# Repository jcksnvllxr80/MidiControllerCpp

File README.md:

# MidiController (C++)

Portable C++17 rewrite of a guitar-pedal MIDI controller's brain, ported from the
Raspberry Pi Python version. Hexagonal design: a hardware-free domain core with all
I/O behind interfaces, so the same code runs on the desktop sim now and a
microcontroller later.

Status: domain core + config + simulator are done and tested; the microcontroller
firmware (Pico 2 W / RP2350) builds and is under hardware bring-up. (The editor app
is a separate project.)
Roadmap: [docs/plan.md](docs/plan.md).

## Build, test, run (WSL)

The **firmware** builds with CMake + the Pico SDK; the **simulator** and the **tests**
build with `g++` (C++17) — GoogleTest and nlohmann/json are vendored, so the host
build has no other dependencies.

```sh
make build       # firmware  -> build-pico/midicontroller_pico.uf2  (Pico 2 W; needs PICO_SDK_PATH)
make build-sim   # simulator  -> build/midicontroller
make test        # build & run all tests (unit + mock + e2e)
make run         # run the simulator on data/ (scripted demo)
make clean       # remove desktop build/ ;  make pico-clean removes build-pico/
```

Flashing and wiring: [docs/mcu.md](docs/mcu.md) and [docs/wiring.md](docs/wiring.md).

## CI & releases

GitHub Actions ([`.github/workflows/ci.yml`](.github/workflows/ci.yml)) runs the host test
suite and builds the firmware `.uf2` on every push and PR. On a push to `master`, once both
pass, it cuts a GitHub **Release** `v<VERSION>` (from the [`VERSION`](VERSION) file) with the
versioned `.uf2` attached — **only when `VERSION` changed** (the tag is new). To ship: bump
`VERSION` and merge to `master`.

## Layout

```
include/mc/   headers: domain/ ports/ config/ adapters/ app/
src/          implementations + main.cpp
data/         config as JSON: midi_controller.json, pedals/, songs/, sets/
tests/        unit/ mock/ e2e/ support/
tools/        yaml2json.py (YAML→JSON), embed_data.py (bake data into flash), gen_font.py, gen_wiring_excalidraw.py
third_party/  vendored googletest + nlohmann/json
docs/         plan, architecture, domain, midi-protocol, config-format, mcu, wiring, wifi-app-handoff
```

## Notes

- The MIDI output matches the original Python byte-for-byte, including its quirks
  (e.g. `Set Preset`'s `cc:0` bank is never sent). See [docs/midi-protocol.md](docs/midi-protocol.md).
- `data/*.json` is generated from the original YAML by `tools/yaml2json.py` and committed.

## Docs

- [docs/architecture.md](docs/architecture.md) — ports & adapters + data-flow diagrams (mermaid)
- [docs/domain.md](docs/domain.md) — the core modules
- [docs/midi-protocol.md](docs/midi-protocol.md) — byte construction & dispatch
- [docs/config-format.md](docs/config-format.md) — JSON config reference
- [docs/mcu.md](docs/mcu.md) — firmware build/flash, adapters, hardware status
- [docs/wiring.md](docs/wiring.md) — Pico 2 W pin map, parts, power (+ `wiring.excalidraw` diagram)
- [docs/wifi-app-handoff.md](docs/wifi-app-handoff.md) — editor-app protocol contract (WiFi, device discovery, firmware update)

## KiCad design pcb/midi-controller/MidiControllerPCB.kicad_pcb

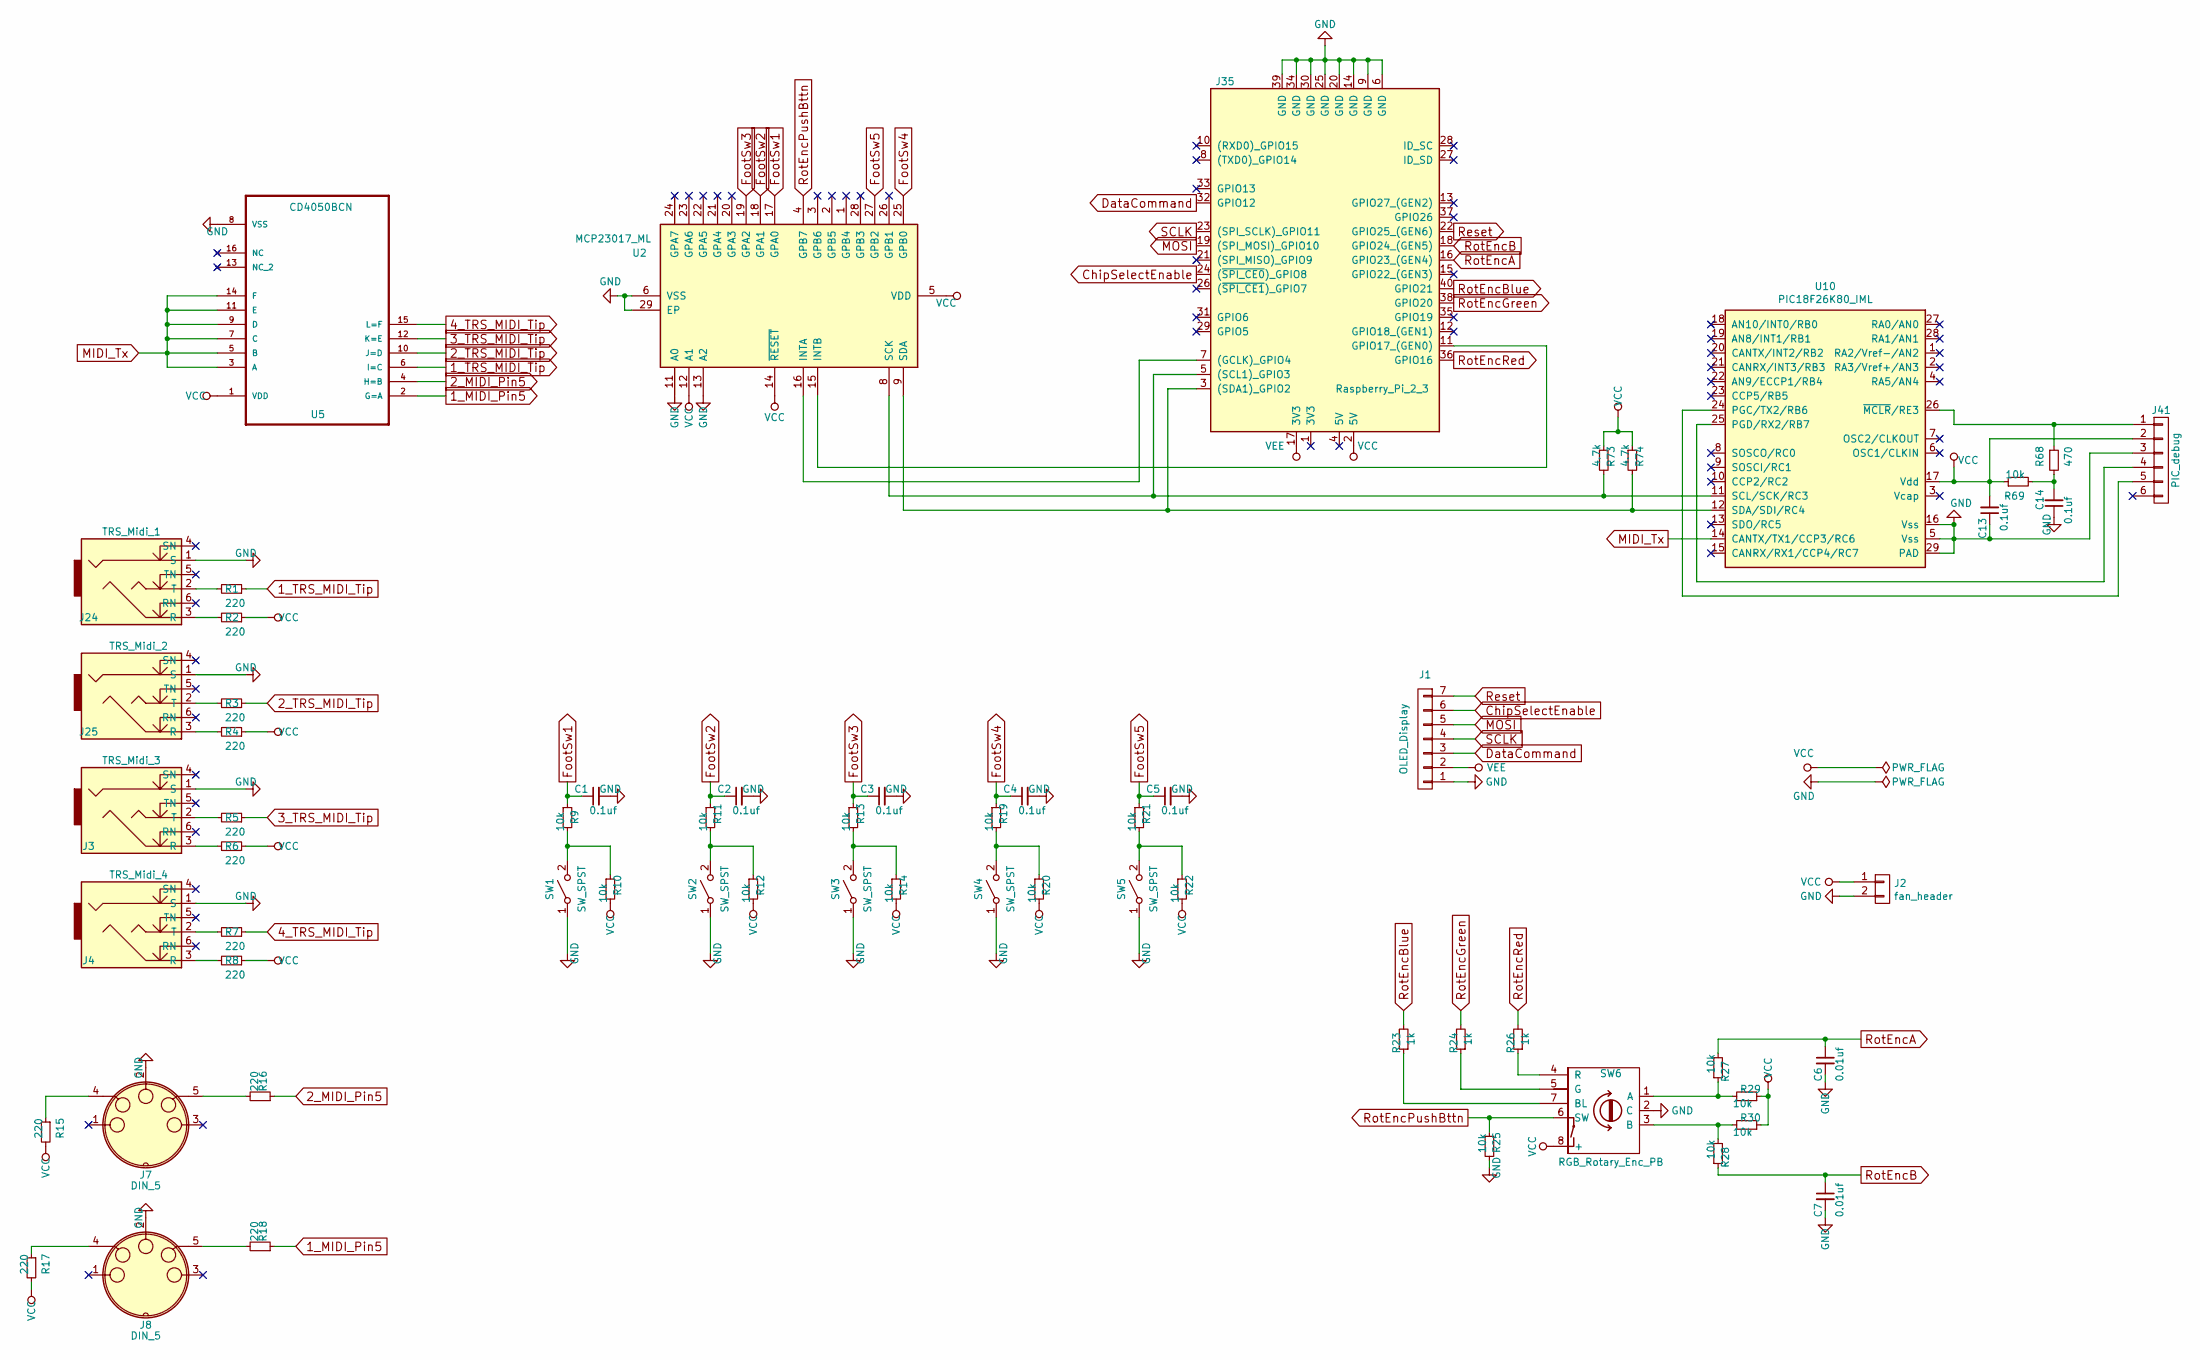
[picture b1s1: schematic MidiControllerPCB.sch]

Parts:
C1, C2, C3, C4, C5, C13, C14: 0.1uf; C_1206_HandSoldering
C6, C7: 0.01uf; C_1206_HandSoldering
J1: OLED_Display; Pin_Header_Straight_1x07_Pitch1.27mm
J2: fan_header; Pin_Header_Straight_1x02_Pitch2.54mm
J3: TRS_Midi_3; NRJ6HM-1-PRE
J4: TRS_Midi_4; NRJ6HM-1-PRE
J7, J8: DIN_5; Midi-Connector
J24: TRS_Midi_1; NRJ6HM-1-PRE
J25: TRS_Midi_2; NRJ6HM-1-PRE
J35: Raspberry_Pi_2_3; Pin_Header_Straight_2x20_Pitch2.54mm
J41: PIC_debug; Pin_Header_Straight_1x06_Pitch2.54mm
R1, R2, R3, R4, R5, R6, R7, R8, R15, R16, R17, R18: 220; R_1206_HandSoldering
R9, R10, R11, R12, R13, R14, R19, R20, R21, R22, R25, R27, R28, R29, R30, R69: 10k; R_1206_HandSoldering
R23, R24, R26: 1k; R_1206_HandSoldering
R68: 470; R_1206_HandSoldering
R73, R74: 4.7k; R_1206_HandSoldering
SW1, SW2, SW3, SW4, SW5: SW_SPST; Pin_Header_Straight_1x02_Pitch2.54mm
SW6: RGB_Rotary_Enc_PB; Pin_Header_Straight_2x04_Pitch2.54mm
U2: MCP23017_ML; QFN-28-1EP_6x6mm_Pitch0.65mm
U5: CD4050BCN; TSSOP-16_4.4x5mm_Pitch0.65mm
U10: PIC18F26K80_IML; QFN-28-1EP_6x6mm_Pitch0.65mm

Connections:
1_MIDI_Pin5: R18.1, U5.2 (G=A)
1_TRS_MIDI_Tip: R1.1, U5.6 (I=C)
2_MIDI_Pin5: R16.1, U5.4 (H=B)
2_TRS_MIDI_Tip: R3.1, U5.10 (J=D)
3_TRS_MIDI_Tip: R5.1, U5.12 (K=E)
4_TRS_MIDI_Tip: R7.1, U5.15 (L=F)
ChipSelectEnable: J1.6, J35.24 ((~SPI_CE0~)_GPIO8)
DataCommand: J1.3, J35.32 (GPIO12)
FootSw1: C1.1, R9.1, U2.17 (GPA0)
FootSw2: C2.1, R11.1, U2.18 (GPA1)
FootSw3: C3.1, R13.1, U2.19 (GPA2)
FootSw4: C4.1, R19.1, U2.25 (GPB0)
FootSw5: C5.1, R21.1, U2.27 (GPB2)
GND: C1.2, C2.2, C3.2, C4.2, C5.2, C6.2, C7.2, C13.1, C14.1, J1.1, J2.2, J3.1 (S), J4.1 (S), J7.2, J8.2, J24.1 (S), J25.1 (S), J35.6 (GND), J35.9 (GND), J35.14 (GND), J35.20 (GND), J35.25 (GND), J35.30 (GND), J35.34 (GND), J35.39 (GND), J41.3, R25.2, SW1.1 (A), SW2.1 (A), SW3.1 (A), SW4.1 (A), SW5.1 (A), SW6.2 (C), U2.6 (VSS), U2.11 (A0), U2.13 (A2), U2.29 (EP), U5.8 (VSS), U10.5 (Vss), U10.16 (Vss), U10.29 (PAD)
MIDI_Tx: U5.3 (A), U5.5 (B), U5.7 (C), U5.9 (D), U5.11 (E), U5.14 (F), U10.14 (CANTX/TX1/CCP3/RC6)
MOSI: J1.5, J35.19 ((SPI_MOSI)_GPIO10)
unnamed: C14.2, R68.2, R69.2
unnamed: J3.2 (T), R5.2
unnamed: J3.3 (R), R6.2
unnamed: J4.2 (T), R7.2
unnamed: J4.3 (R), R8.2
unnamed: J7.4, R15.1
unnamed: J7.5, R16.2
unnamed: J8.4, R17.1
unnamed: J8.5, R18.2
unnamed: J24.2 (T), R1.2
unnamed: J24.3 (R), R2.2
unnamed: J25.2 (T), R3.2
unnamed: J25.3 (R), R4.2
unnamed: J35.3 ((SDA1)_GPIO2), R74.2, U2.9 (SDA), U10.12 (SDA/SDI/RC4)
unnamed: J35.5 ((SCL1)_GPIO3), R73.2, U2.8 (SCK), U10.11 (SCL/SCK/RC3)
unnamed: J35.7 ((GCLK)_GPIO4), U2.16 (INTA)
unnamed: J35.11 (GPIO17_(GEN0)), U2.15 (INTB)
unnamed: J41.1, R68.1, U10.26 (~MCLR~/RE3)
unnamed: J41.4, U10.25 (PGD/RX2/RB7)
unnamed: J41.5, U10.24 (PGC/TX2/RB6)
unnamed: R9.2, R10.1, SW1.2 (B)
unnamed: R11.2, R12.1, SW2.2 (B)
unnamed: R13.2, R14.1, SW3.2 (B)
unnamed: R19.2, R20.1, SW4.2 (B)
unnamed: R21.2, R22.1, SW5.2 (B)
unnamed: R23.1, SW6.7 (BL)
unnamed: R24.1, SW6.5 (G)
unnamed: R26.1, SW6.4 (R)
unnamed: R27.1, R29.2, SW6.1 (A)
unnamed: R28.2, R30.2, SW6.3 (B)
Reset: J1.7, J35.22 (GPIO25_(GEN6))
RotEncA: C6.1, J35.16 (GPIO23_(GEN4)), R27.2
RotEncB: C7.1, J35.18 (GPIO24_(GEN5)), R28.1
RotEncBlue: J35.40 (GPIO21), R23.2
RotEncGreen: J35.38 (GPIO20), R24.2
RotEncPushBttn: R25.1, SW6.6 (SW), U2.4 (GPB7)
RotEncRed: J35.36 (GPIO16), R26.2
SCLK: J1.4, J35.23 ((SPI_SCLK)_GPIO11)
VCC: C13.2, J2.1, J35.2 (5V), J41.2, R2.1, R4.1, R6.1, R8.1, R10.2, R12.2, R14.2, R15.2, R17.2, R20.2, R22.2, R29.1, R30.1, R69.1, R73.1, R74.1, SW6.8 (+), U2.5 (VDD), U2.12 (A1), U2.14 (~RESET~), U5.1 (VDD), U10.17 (Vdd)
VEE: J1.2, J35.17 (3V3)

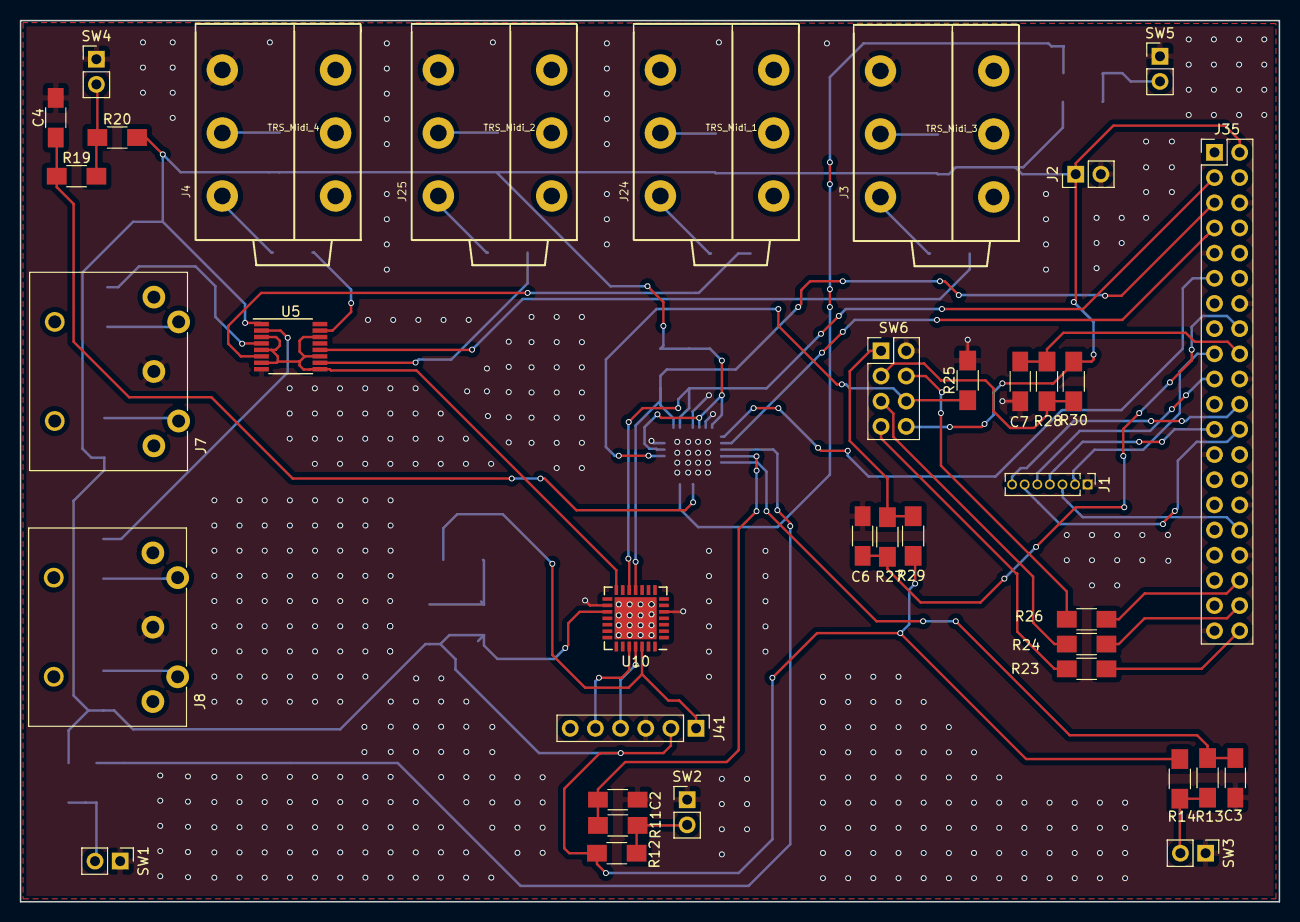
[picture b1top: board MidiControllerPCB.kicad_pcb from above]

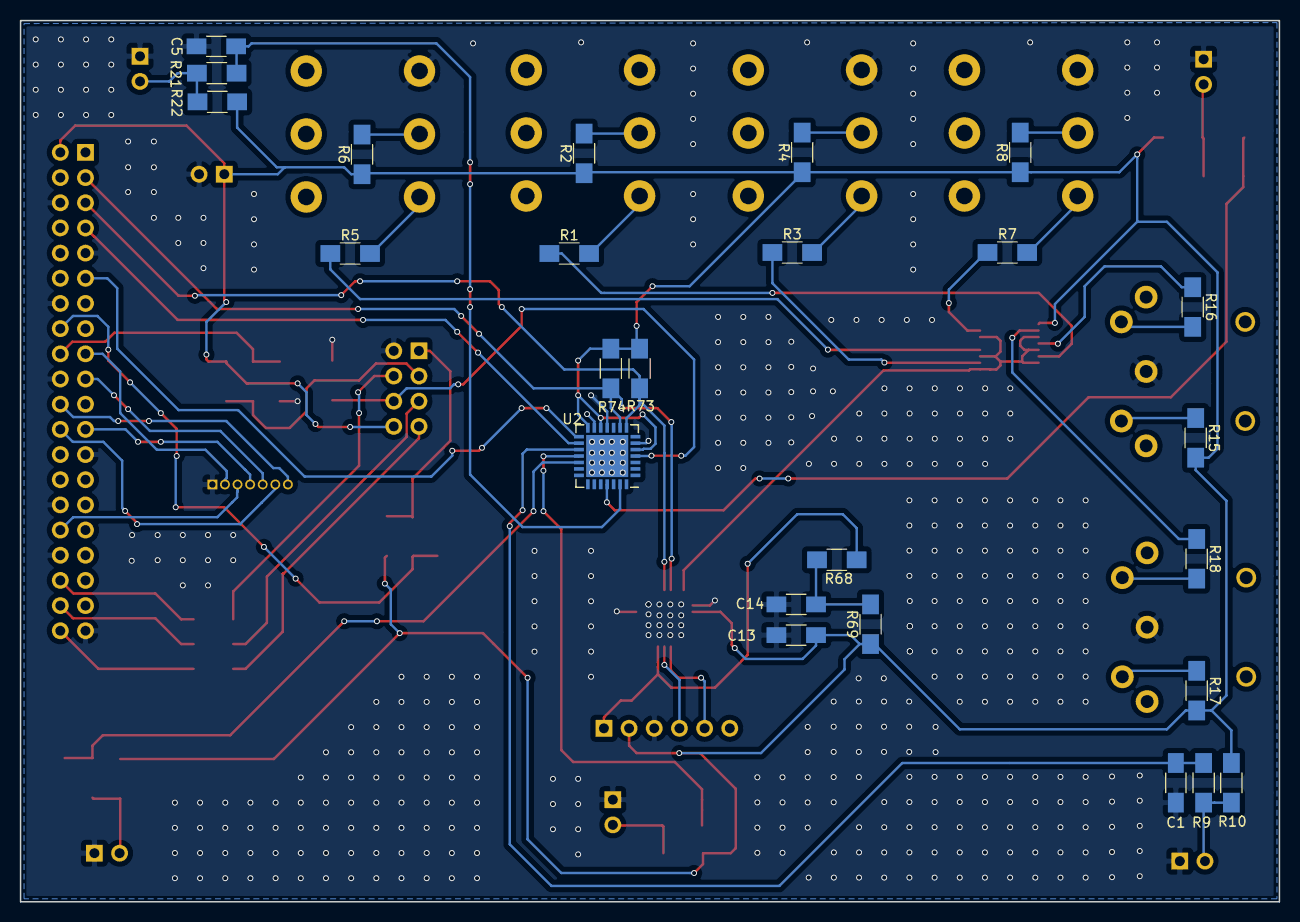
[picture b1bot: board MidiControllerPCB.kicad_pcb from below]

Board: 2 copper layers, 127.0 x 88.9 mm, 62 parts (25 on the bottom side), 56 nets.

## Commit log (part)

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2026-06-07 implementation
2026-06-07 Add unit tests for MenuTree, MidiMessage, PedalConfig, and Transform
    - Introduced comprehensive tests for MenuTree covering node helpers, message variants, and error handling.
    - Added tests for MidiMessage to validate data-byte handling and parameterized coverage for control and program changes.
    - Implemented tests for PedalConfig to verify action helpers and structural assertions on real configurations.
    - Created tests for Transform to ensure arithmetic operations, dictionary lookups, and error handling for malformed expressions.
    - Added tests for Value variant to check predicates, accessors, string conversion, and equality checks.
2026-06-07 Update documentation to clarify project structure and external editor app relationship
2026-06-14 Add C++ MidiController firmware: domain core, sim, tests, Pico 2 W scaffold
    Port the Raspberry Pi Python "brain" to a portable, hardware-free C++17 core
    behind ports & adapters. MIDI output matches the Python byte-for-byte
    (including its cc:0 "bank select" quirk).
    - domain: MidiMessage, Value, Transform (safe parser, no eval/regex),
    PedalConfig, MidiPedal dispatch, Setlist/Song/Part, ButtonSM, ControllerState,
    MenuTree
2026-06-14 Implement EditorProtocol and StdioConfigTransport for USB CDC communication; update Application to handle display messages and add tests for protocol functionality
2026-06-14 bugfix: make serial actually work
2026-06-14 feat: add WiFi support with EditorProtocol integration and mDNS discovery
2026-06-14 feat: Update USB configuration for raw-USB editor link
    - Modified `tusb_config.h` to configure a single VENDOR interface for the USB editor link, disabling CDC and enabling vendor-specific endpoints.
    - Updated `usb_descriptors.c` to define descriptors for the new VENDOR interface, including MS-OS-2.0 descriptors for Windows auto-binding to WinUSB.
    - Adjusted buffer sizes for vendor communication to accommodate larger data transfers.
    - Enhanced error handling in `Application.cpp` to prevent crash loops on malformed configurations, allowing fallback to a safe state.
    - Implemented new methods in `FsConfigStore` for removing configuration files.
    - Added functionality in `EditorProtocol` to handl
2026-06-14 feat: Implement system control for rebooting and bootloader access; update EditorProtocol for device identification and add tests
2026-06-14 feat: Update documentation to reflect new tools and architecture changes; enhance MCU and WiFi integration details
2026-06-14 feat: Add CI workflow for building firmware and running tests; include versioning for releases
2026-06-14 Integrate/bare metal pico 2w (#1)
    * Add C++ MidiController firmware: domain core, sim, tests, Pico 2 W scaffold
    Port the Raspberry Pi Python "brain" to a portable, hardware-free C++17 core
    behind ports & adapters. MIDI output matches the Python byte-for-byte
    (including its cc:0 "bank select" quirk).
    - domain: MidiMessage, Value, Transform (safe parser, no eval/regex),
    PedalConfig, MidiPedal dispatch, Setlist/Song/Part, ButtonSM, ControllerState,
2026-06-14 Update flashing instructions for Pico 2 W to clarify initial setup and BOOTSEL process
2026-06-14 Refactor CI workflow to consolidate build paths for push and pull request triggers
2026-06-16 add midicontroller pcb
2026-06-16 Refactor Pico 2 W firmware to drive the real PCB (MCP23017 over I²C, MIDI via PIC bridge, SPI OLED) and remove the fictional tempo-output port
2026-06-16 Remove cooling fan from Pico 2 W conversion documentation, clarifying that the RP2350 runs cold and requires no active cooling.
2026-06-21 Add script to convert BDF fonts to C++ header with bitmap data
    This commit introduces a new Python script, `bdf_to_header.py`, which converts monospace BDF fonts into a C++ header file containing fixed-cell bitmap representations. The script parses the BDF forma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
2026-06-21 Refactor MCP expander and input handling for improved encoder and button state management
2026-06-21 Refactor input handling to improve GPIO state management and ensure reliable first press detection
2026-06-21 Bump version to 0.1.1
2026-06-23 Refactor encoder handling for improved state management and debounce logic; optimize display message rendering to prevent unnecessary redraws
